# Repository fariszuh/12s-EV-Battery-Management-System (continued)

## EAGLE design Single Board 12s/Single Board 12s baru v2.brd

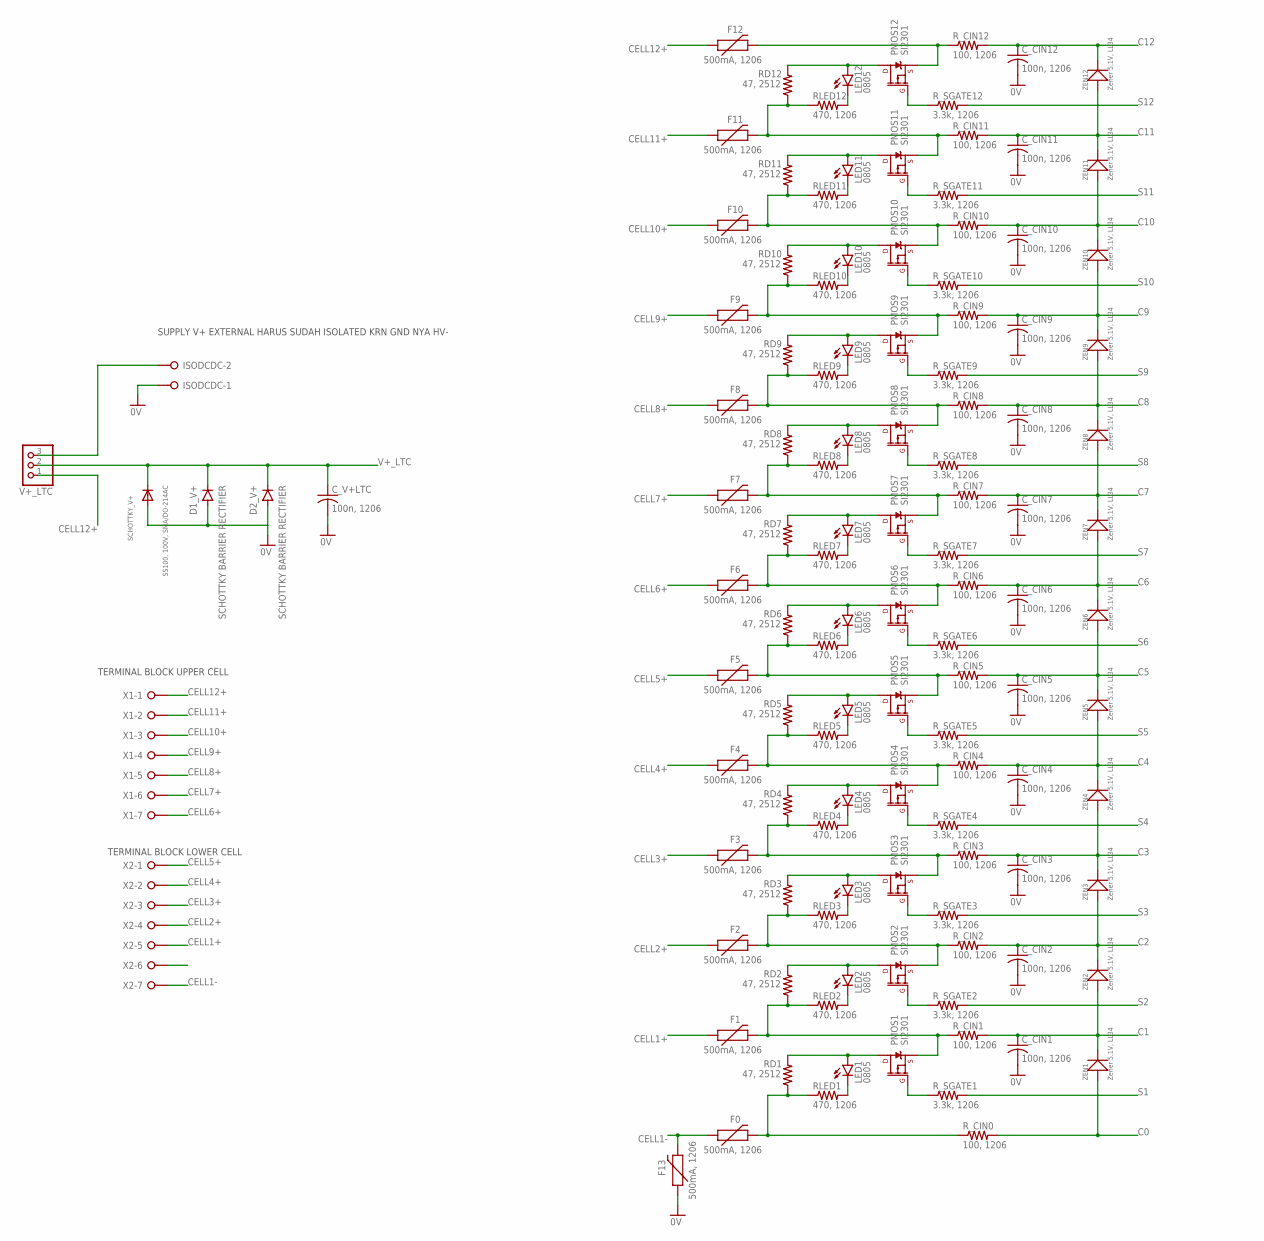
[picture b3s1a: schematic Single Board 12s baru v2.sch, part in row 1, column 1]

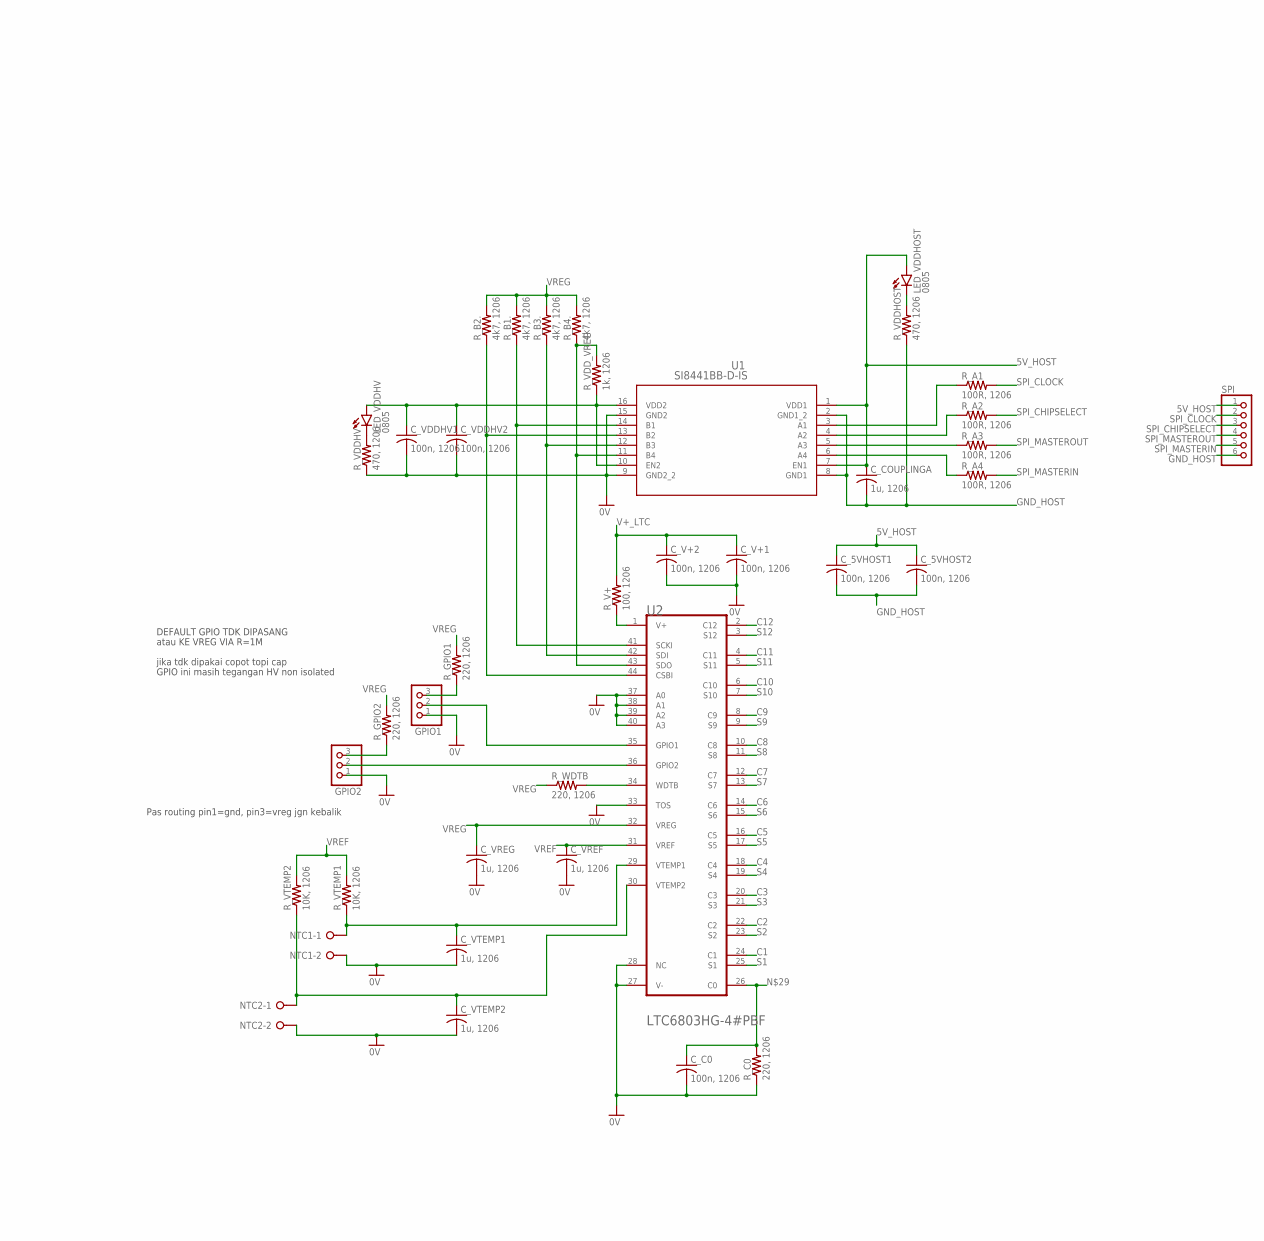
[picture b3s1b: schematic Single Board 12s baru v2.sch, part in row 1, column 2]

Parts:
C_5VHOST1, C_5VHOST2: 100n, 1206; C1206
C_C0: 100n, 1206; C1206
C_CIN1, C_CIN2, C_CIN3, C_CIN4, C_CIN5, C_CIN6, C_CIN7, C_CIN8, C_CIN9, C_CIN10, C_CIN11, C_CIN12: 100n, 1206; C1206
C_COUPLINGA: 1u, 1206; C1206
C_V+1, C_V+2: 100n, 1206; C1206
C_V+LTC: 100n, 1206; C1206
C_VDDHV1, C_VDDHV2: 100n, 1206; C1206
C_VREF: 1u, 1206; C1206
C_VREG: 1u, 1206; C1206
C_VTEMP1, C_VTEMP2: 1u, 1206; C1206
D1_V+, D2_V+: SCHOTTKY BARRIER RECTIFIER; DO27-15
F0, F1, F2, F3, F4, F5, F6, F7, F8, F9, F10, F11, F12, F13: 500mA, 1206; 1206
GPIO1, GPIO2: PINHD-1X3; 1X03
ISODCDC: W237-02P; W237-132
LED1, LED2, LED3, LED4, LED5, LED6, LED7, LED8, LED9, LED10, LED11, LED12: 0805; SML0805
LED_VDDHOST: 0805; SML0805
LED_VDDHV: 0805; SML0805
NTC1, NTC2: W237-02P; W237-132
PMOS1, PMOS2, PMOS3, PMOS4, PMOS5, PMOS6, PMOS7, PMOS8, PMOS9, PMOS10, PMOS11, PMOS12: SI2301; SOT23-3
RD1, RD2, RD3, RD4, RD5, RD6, RD7, RD8, RD9, RD10, RD11, RD12: 47, 2512; R2512
RLED1, RLED2, RLED3, RLED4, RLED5, RLED6, RLED7, RLED8, RLED9, RLED10, RLED11, RLED12: 470, 1206; R1206
R_A1, R_A2, R_A3, R_A4: 100R, 1206; R1206
R_B1., R_B2., R_B3., R_B4.: 4k7, 1206; R1206
R_C0: 220, 1206; R1206
R_CIN0, R_CIN1, R_CIN2, R_CIN3, R_CIN4, R_CIN5, R_CIN6, R_CIN7, R_CIN8, R_CIN9, R_CIN10, R_CIN11, R_CIN12: 100, 1206; R1206
R_GPIO1, R_GPIO2: 220, 1206; R1206
R_SGATE1, R_SGATE2, R_SGATE3, R_SGATE4, R_SGATE5, R_SGATE6, R_SGATE7, R_SGATE8, R_SGATE9, R_SGATE10, R_SGATE11, R_SGATE12: 3.3k, 1206; R1206
R_V+: 100, 1206; R1206
R_VDDHOST: 470, 1206; R1206
R_VDDHV: 470, 1206; R1206
R_VDD_VREG: 1k, 1206; R1206
R_VTEMP1, R_VTEMP2: 10K, 1206; R1206
R_WDTB: 220, 1206; R1206
SCHOTTKY_V+: SS100, 100V, SMA/DO-214AC; SMADIODE
SPI: PINHD-1X6; 1X06
U1: SI8441BB-D-IS; SOIC-16W_SIL
U2: LINEAR_TECHNOLOGY_LTC6803HG-4#PBFLINEAR_TECHNOLOG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; LINEAR_TECHNOLOGY_LTC6803HG-4#PBF_2
V+_LTC: PINHD-1X3; 1X03
X1, X2: W237-07P; W237-7P
ZEN1, ZEN2, ZEN3, ZEN4, ZEN5, ZEN6, ZEN7, ZEN8, ZEN9, ZEN10, ZEN11, ZEN12: Zener 5.1V, LL34; LL-34

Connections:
0V: C_C0.2, C_CIN1.2, C_CIN2.2, C_CIN3.2, C_CIN4.2, C_CIN5.2, C_CIN6.2, C_CIN7.2, C_CIN8.2, C_CIN9.2, C_CIN10.2, C_CIN11.2, C_CIN12.2, C_V+1.2, C_V+2.2, C_V+LTC.2, C_VDDHV1.2, C_VDDHV2.2, C_VREF.2, C_VREG.2, C_VTEMP1.2, C_VTEMP2.2, D1_V+.A, D2_V+.A, F13.1, GPIO1.1, GPIO2.1, ISODCDC.1, NTC1.2, NTC2.2, R_C0.1, R_VDDHV.1, SCHOTTKY_V+.A, U1.9 (GND2_2), U1.15 (GND2), U2.27 (V-), U2.28 (NC), U2.33 (TOS), U2.37 (A0), U2.38 (A1), U2.39 (A2), U2.40 (A3)
5V_HOST: C_5VHOST1.1, C_5VHOST2.1, C_COUPLINGA.1, LED_VDDHOST.A, SPI.1, U1.1 (VDD1), U1.7 (EN1)
C0: R_CIN0.2, ZEN1.A (+)
C1: C_CIN1.1, R_CIN1.2, U2.24 (C1), ZEN1.C (-), ZEN2.A (+)
C2: C_CIN2.1, R_CIN2.2, U2.22 (C2), ZEN2.C (-), ZEN3.A (+)
C3: C_CIN3.1, R_CIN3.2, U2.20 (C3), ZEN3.C (-), ZEN4.A (+)
C4: C_CIN4.1, R_CIN4.2, U2.18 (C4), ZEN4.C (-), ZEN5.A (+)
C5: C_CIN5.1, R_CIN5.2, U2.16 (C5), ZEN5.C (-), ZEN6.A (+)
C6: C_CIN6.1, R_CIN6.2, U2.14 (C6), ZEN6.C (-), ZEN7.A (+)
C7: C_CIN7.1, R_CIN7.2, U2.12 (C7), ZEN7.C (-), ZEN8.A (+)
C8: C_CIN8.1, R_CIN8.2, U2.10 (C8), ZEN8.C (-), ZEN9.A (+)
C9: C_CIN9.1, R_CIN9.2, U2.8 (C9), ZEN9.C (-), ZEN10.A (+)
C10: C_CIN10.1, R_CIN10.2, U2.6 (C10), ZEN10.C (-), ZEN11.A (+)
C11: C_CIN11.1, R_CIN11.2, U2.4 (C11), ZEN11.C (-), ZEN12.A (+)
C12: C_CIN12.1, R_CIN12.2, U2.2 (C12), ZEN12.C (-)
CELL1+: F1.1, X2.5
CELL1-: F0.1, F13.2, X2.7
CELL2+: F2.1, X2.4
CELL3+: F3.1, X2.3
CELL4+: F4.1, X2.2
CELL5+: F5.1, X2.1
CELL6+: F6.1, X1.7
CELL7+: F7.1, X1.6
CELL8+: F8.1, X1.5
CELL9+: F9.1, X1.4
CELL10+: F10.1, X1.3
CELL11+: F11.1, X1.2
CELL12+: F12.1, V+_LTC.1, X1.1
GND_HOST: C_5VHOST1.2, C_5VHOST2.2, C_COUPLINGA.2, R_VDDHOST.1, SPI.6, U1.2 (GND1_2), U1.8 (GND1)
unnamed: R_V+.1, U2.1 (V+)
unnamed: PMOS1.1 (G), R_SGATE1.1
unnamed: LED1.A, PMOS1.3 (D), RD1.2
unnamed: R_A2.1, U1.4 (A2)
unnamed: LED_VDDHOST.C, R_VDDHOST.2
unnamed: LED1.C, RLED1.2
unnamed: F0.2, RD1.1, RLED1.1, R_CIN0.1
unnamed: R_WDTB.2, U2.34 (WDTB)
unnamed: ISODCDC.2, V+_LTC.3
unnamed: LED_VDDHV.C, R_VDDHV.2
unnamed: PMOS2.1 (G), R_SGATE2.1
unnamed: R_B4..1, R_VDD_VREG.2, U1.11 (B4), U2.43 (SDO)
unnamed: LED2.A, PMOS2.3 (D), RD2.2
unnamed: LED2.C, RLED2.2
unnamed: F1.2, PMOS1.2 (S), RD2.1, RLED2.1, R_CIN1.1
unnamed: R_B3..1, U1.12 (B3), U2.42 (SDI)
unnamed: R_B2..1, U1.13 (B2), U2.44 (CSBI)
unnamed: PMOS3.1 (G), R_SGATE3.1
unnamed: R_B1..1, U1.14 (B1), U2.41 (SCKI)
unnamed: R_A3.1, U1.5 (A3)
unnamed: R_A1.1, U1.3 (A1)
unnamed: LED3.A, PMOS3.3 (D), RD3.2
unnamed: LED3.C, RLED3.2
unnamed: F2.2, PMOS2.2 (S), RD3.1, RLED3.1, R_CIN2.1
unnamed: R_A4.1, U1.6 (A4)
unnamed: C_C0.1, R_C0.2, U2.26 (C0)
unnamed: PMOS4.1 (G), R_SGATE4.1
unnamed: GPIO2.2, U2.36 (GPIO2)
unnamed: GPIO1.2, U2.35 (GPIO1)
unnamed: C_VTEMP2.1, NTC2.1, R_VTEMP2.1, U2.30 (VTEMP2)
unnamed: LED4.A, PMOS4.3 (D), RD4.2
unnamed: LED4.C, RLED4.2
unnamed: F3.2, PMOS3.2 (S), RD4.1, RLED4.1, R_CIN3.1
unnamed: C_VTEMP1.1, NTC1.1, R_VTEMP1.1, U2.29 (VTEMP1)
unnamed: GPIO2.3, R_GPIO2.1
unnamed: PMOS5.1 (G), R_SGATE5.1
unnamed: GPIO1.3, R_GPIO1.1
unnamed: LED5.A, PMOS5.3 (D), RD5.2
unnamed: LED5.C, RLED5.2
unnamed: F4.2, PMOS4.2 (S), RD5.1, RLED5.1, R_CIN4.1
unnamed: PMOS6.1 (G), R_SGATE6.1
unnamed: LED6.A, PMOS6.3 (D), RD6.2
unnamed: LED6.C, RLED6.2
unnamed: F5.2, PMOS5.2 (S), RD6.1, RLED6.1, R_CIN5.1
unnamed: PMOS7.1 (G), R_SGATE7.1
unnamed: LED7.A, PMOS7.3 (D), RD7.2
unnamed: LED7.C, RLED7.2
unnamed: F6.2, PMOS6.2 (S), RD7.1, RLED7.1, R_CIN6.1
unnamed: PMOS8.1 (G), R_SGATE8.1
unnamed: LED8.A, PMOS8.3 (D), RD8.2
unnamed: LED8.C, RLED8.2
unnamed: F7.2, PMOS7.2 (S), RD8.1, RLED8.1, R_CIN7.1
unnamed: PMOS9.1 (G), R_SGATE9.1
unnamed: LED9.A, PMOS9.3 (D), RD9.2
unnamed: LED9.C, RLED9.2
unnamed: F8.2, PMOS8.2 (S), RD9.1, RLED9.1, R_CIN8.1
unnamed: PMOS10.1 (G), R_SGATE10.1
unnamed: LED10.A, PMOS10.3 (D), RD10.2
unnamed: LED10.C, RLED10.2
unnamed: F9.2, PMOS9.2 (S), RD10.1, RLED10.1, R_CIN9.1
unnamed: PMOS11.1 (G), R_SGATE11.1
unnamed: LED11.A, PMOS11.3 (D), RD11.2
unnamed: LED11.C, RLED11.2
unnamed: F10.2, PMOS10.2 (S), RD11.1, RLED11.1, R_CIN10.1
unnamed: PMOS12.1 (G), R_SGATE12.1
unnamed: F12.2, PMOS12.2 (S), R_CIN12.1
unnamed: LED12.A, PMOS12.3 (D), RD12.2
unnamed: LED12.C, RLED12.2
unnamed: F11.2, PMOS11.2 (S), RD12.1, RLED12.1, R_CIN11.1
S1: R_SGATE1.2, U2.25 (S1)
S2: R_SGATE2.2, U2.23 (S2)
S3: R_SGATE3.2, U2.21 (S3)
S4: R_SGATE4.2, U2.19 (S4)
S5: R_SGATE5.2, U2.17 (S5)
S6: R_SGATE6.2, U2.15 (S6)
S7: R_SGATE7.2, U2.13 (S7)
S8: R_SGATE8.2, U2.11 (S8)
S9: R_SGATE9.2, U2.9 (S9)
S10: R_SGATE10.2, U2.7 (S10)
S11: R_SGATE11.2, U2.5 (S11)
S12: R_SGATE12.2, U2.3 (S12)
SPI_CHIPSELECT: R_A2.2, SPI.3
SPI_CLOCK: R_A1.2, SPI.2
SPI_MASTERIN: R_A4.2, SPI.5
SPI_MASTEROUT: R_A3.2, SPI.4
V+_LTC: C_V+1.1, C_V+2.1, C_V+LTC.1, D1_V+.C, D2_V+.C, R_V+.2, SCHOTTKY_V+.C, V+_LTC.2
VREF: C_VREF.1, R_VTEMP1.2, R_VTEMP2.2, U2.31 (VREF)
VREG: C_VDDHV1.1, C_VDDHV2.1, C_VREG.1, LED_VDDHV.A, R_B1..2, R_B2..2, R_B3..2, R_B4..2, R_GPIO1.2, R_GPIO2.2, R_VDD_VREG.1, R_WDTB.1, U1.10 (EN2), U1.16 (VDD2), U2.32 (VREG)

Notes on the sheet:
DEFAULT GPIO TDK DIPASANG
atau KE VREG VIA R=1M
jika tdk dipakai copot topi cap
GPIO ini masih tegangan HV non isolated
Pas routing pin1=gnd, pin3=vreg jgn kebalik
TERMINAL BLOCK UPPER CELL
TERMINAL BLOCK LOWER CELL
SUPPLY V+ EXTERNAL HARUS SUDAH ISOLATED KRN GND NYA HV-

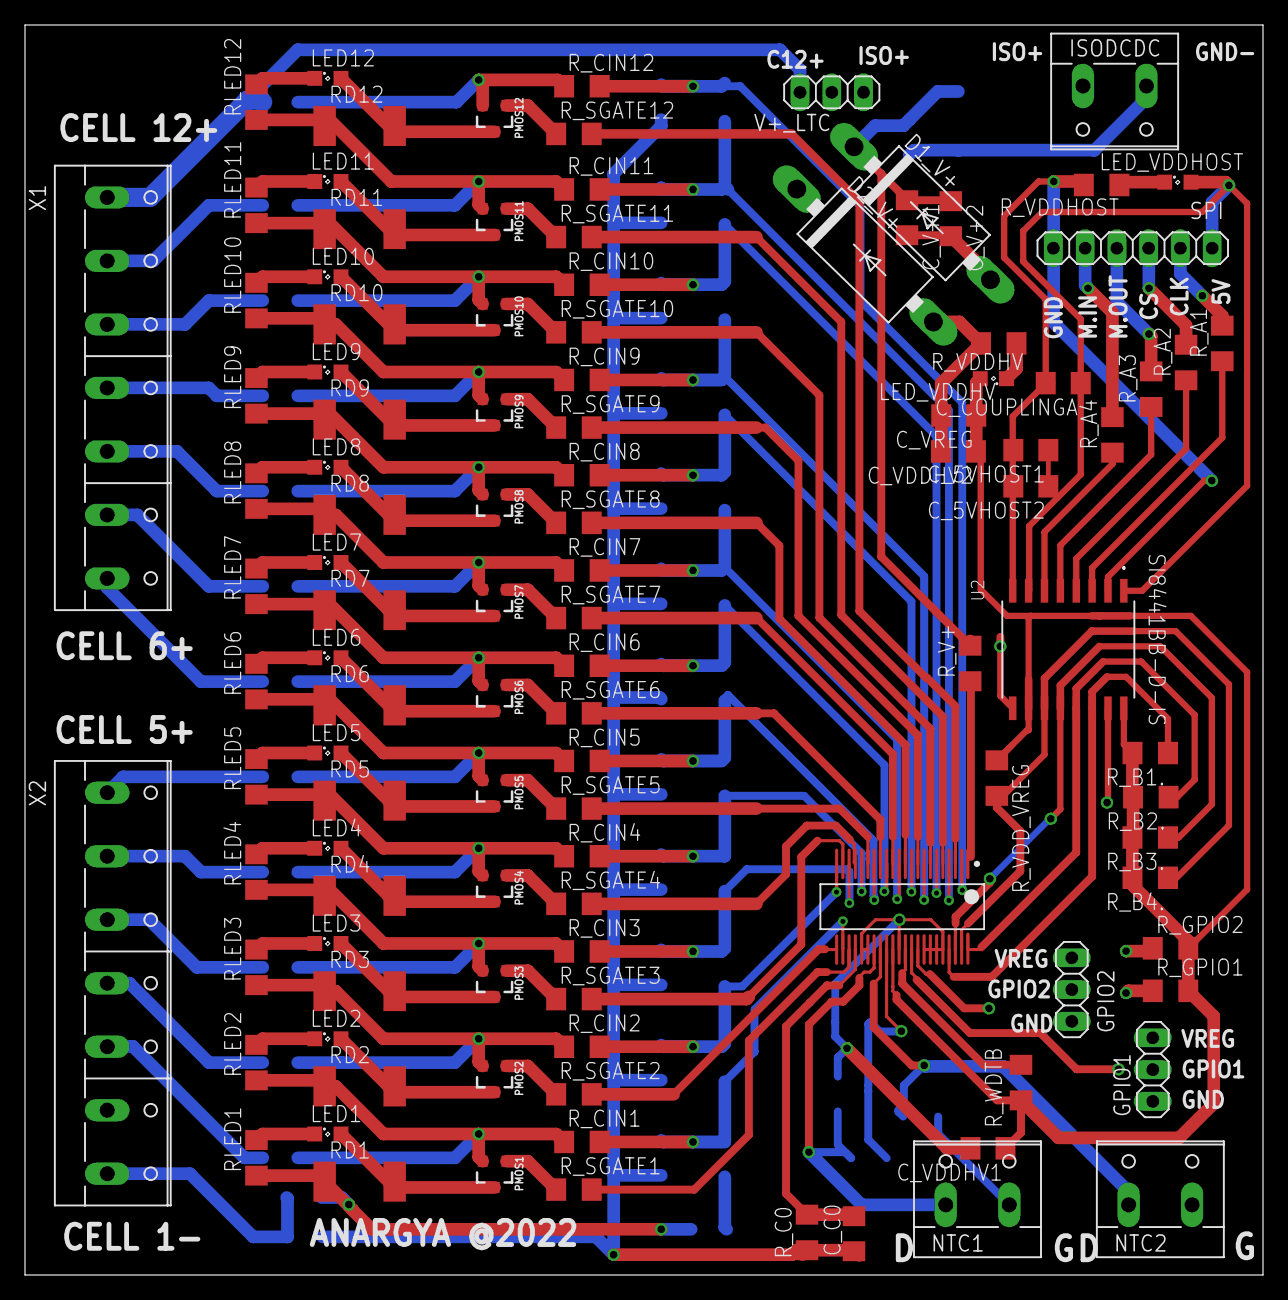
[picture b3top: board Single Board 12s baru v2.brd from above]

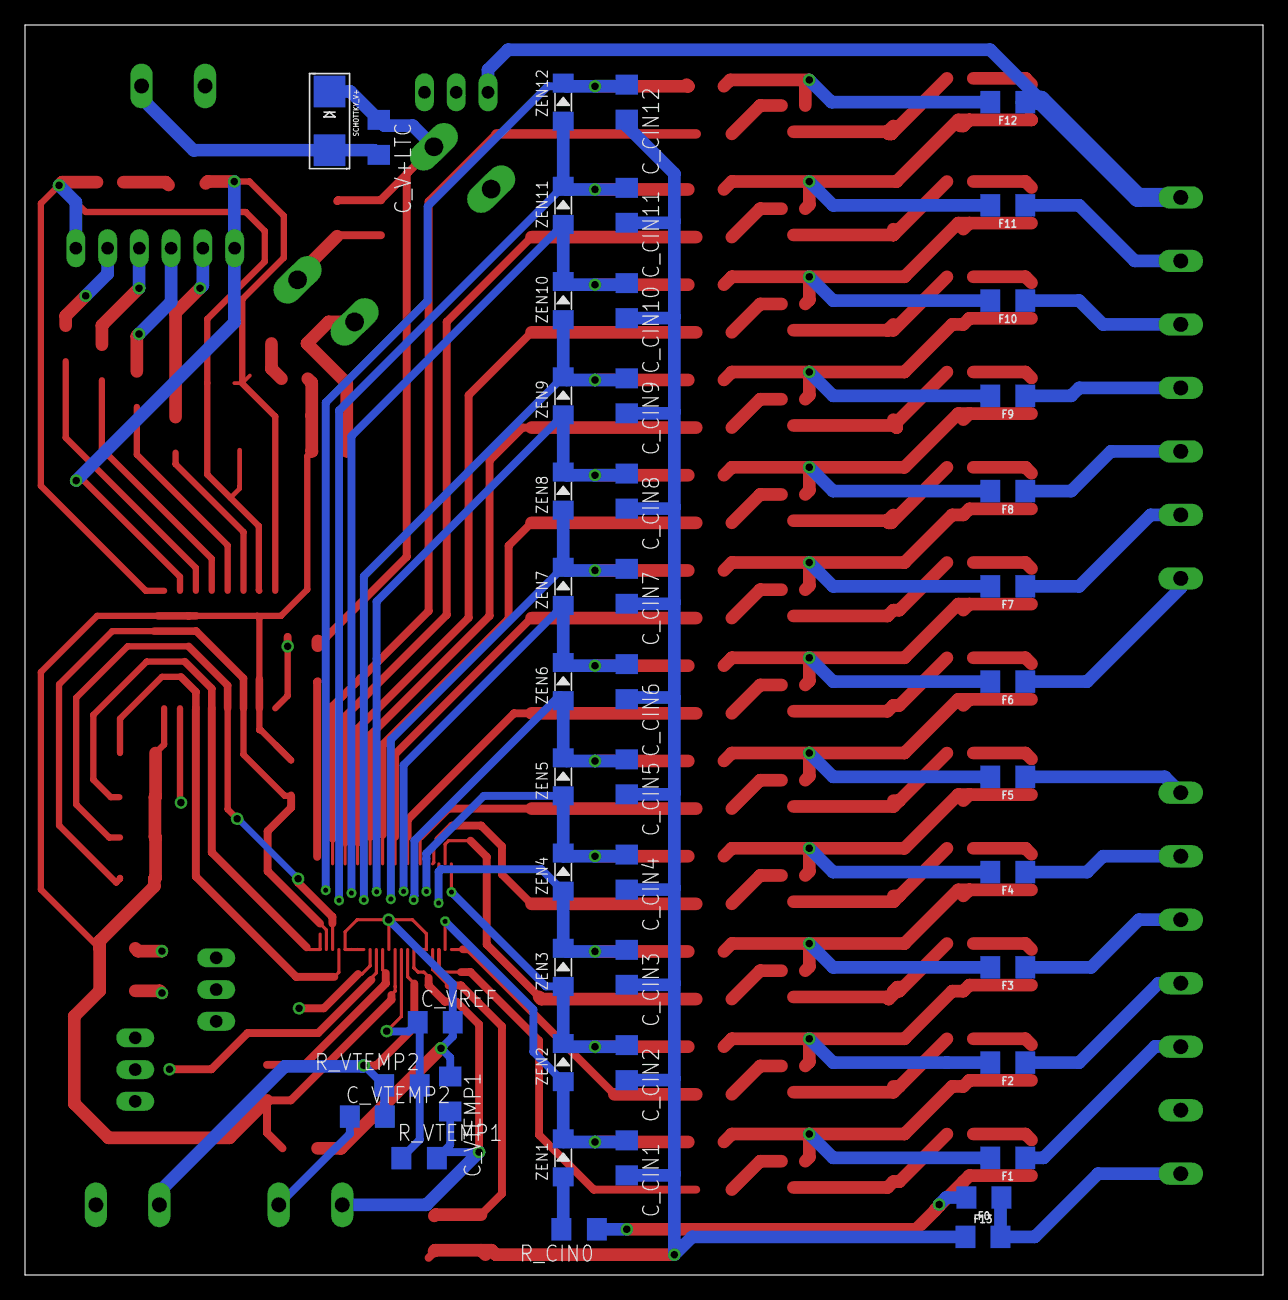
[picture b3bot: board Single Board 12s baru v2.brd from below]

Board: 4 copper layers, 99.0 x 100.0 mm, 158 parts (46 on the bottom side), 117 nets.

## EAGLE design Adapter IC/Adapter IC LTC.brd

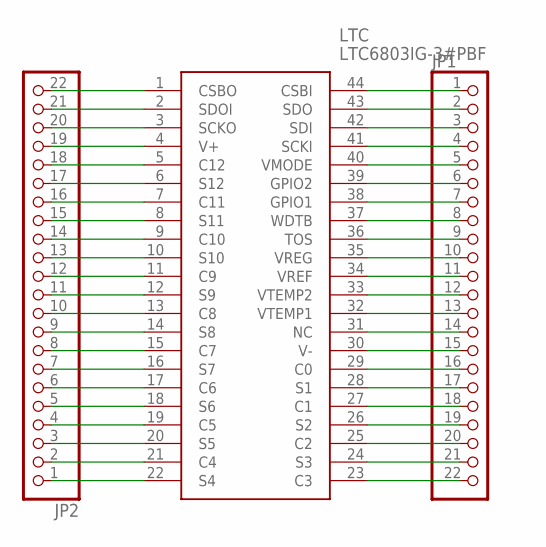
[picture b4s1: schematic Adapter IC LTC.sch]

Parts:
JP1, JP2: PINHD-1X22; 1X22
LTC: LTC6803IG-3#PBF; SOP50P780X185-44N

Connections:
unnamed: JP2.22, LTC.1 (CSBO)
unnamed: JP2.21, LTC.2 (SDOI)
unnamed: JP2.20, LTC.3 (SCKO)
unnamed: JP2.19, LTC.4 (V+)
unnamed: JP2.18, LTC.5 (C12)
unnamed: JP2.17, LTC.6 (S12)
unnamed: JP2.16, LTC.7 (C11)
unnamed: JP2.15, LTC.8 (S11)
unnamed: JP2.14, LTC.9 (C10)
unnamed: JP2.13, LTC.10 (S10)
unnamed: JP2.12, LTC.11 (C9)
unnamed: JP2.11, LTC.12 (S9)
unnamed: JP2.10, LTC.13 (C8)
unnamed: JP2.9, LTC.14 (S8)
unnamed: JP2.8, LTC.15 (C7)
unnamed: JP2.7, LTC.16 (S7)
unnamed: JP2.6, LTC.17 (C6)
unnamed: JP2.5, LTC.18 (S6)
unnamed: JP2.4, LTC.19 (C5)
unnamed: JP2.3, LTC.20 (S5)
unnamed: JP2.2, LTC.21 (C4)
unnamed: JP2.1, LTC.22 (S4)
unnamed: JP1.22, LTC.23 (C3)
unnamed: JP1.21, LTC.24 (S3)
unnamed: JP1.20, LTC.25 (C2)
unnamed: JP1.19, LTC.26 (S2)
unnamed: JP1.18, LTC.27 (C1)
unnamed: JP1.17, LTC.28 (S1)
unnamed: JP1.16, LTC.29 (C0)
unnamed: JP1.15, LTC.30 (V-)
unnamed: JP1.14, LTC.31 (NC)
unnamed: JP1.13, LTC.32 (VTEMP1)
unnamed: JP1.12, LTC.33 (VTEMP2)
unnamed: JP1.11, LTC.34 (VREF)
unnamed: JP1.10, LTC.35 (VREG)
unnamed: JP1.9, LTC.36 (TOS)
unnamed: JP1.7, LTC.38 (GPIO1)
unnamed: JP1.8, LTC.37 (WDTB)
unnamed: JP1.6, LTC.39 (GPIO2)
unnamed: JP1.5, LTC.40 (VMODE)
unnamed: JP1.4, LTC.41 (SCKI)
unnamed: JP1.3, LTC.42 (SDI)
unnamed: JP1.2, LTC.43 (SDO)
unnamed: JP1.1, LTC.44 (CSBI)

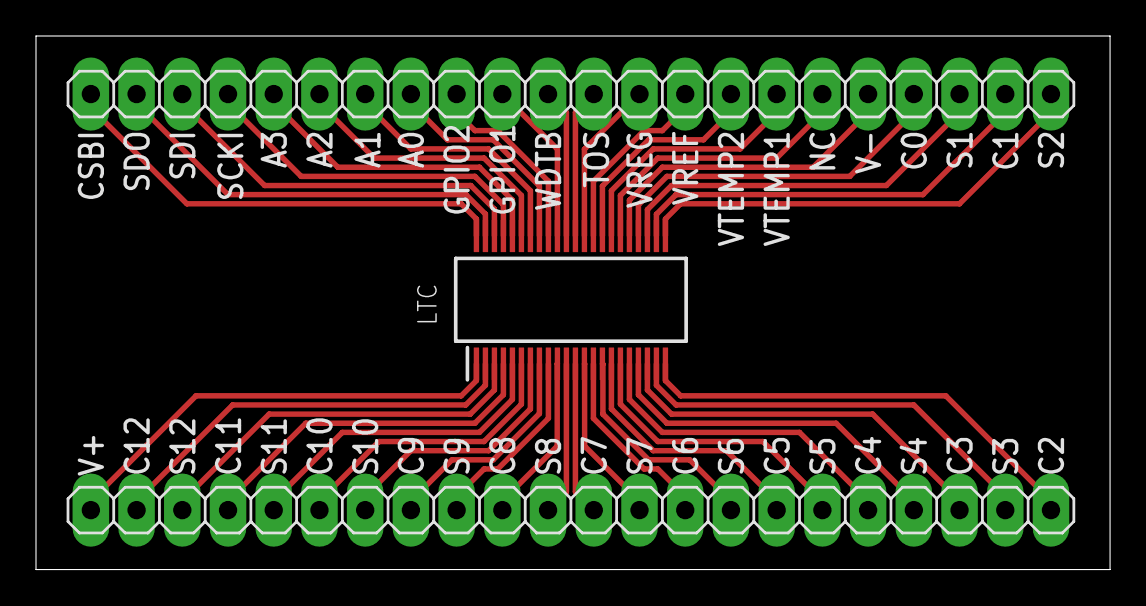
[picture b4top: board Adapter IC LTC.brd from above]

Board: 2 copper layers, 59.7 x 29.6 mm, 3 parts (0 on the bottom side), 44 nets.

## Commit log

2023-09-27 add README.md
2023-09-27 add images to README.md
2023-09-27 revised README.md
2023-11-28 add Voltage Regulator Simulation
2023-11-28 add Journal Reference
2023-11-28 add Balancing SoC Calculation
2023-11-28 add Previous Design as Reference
